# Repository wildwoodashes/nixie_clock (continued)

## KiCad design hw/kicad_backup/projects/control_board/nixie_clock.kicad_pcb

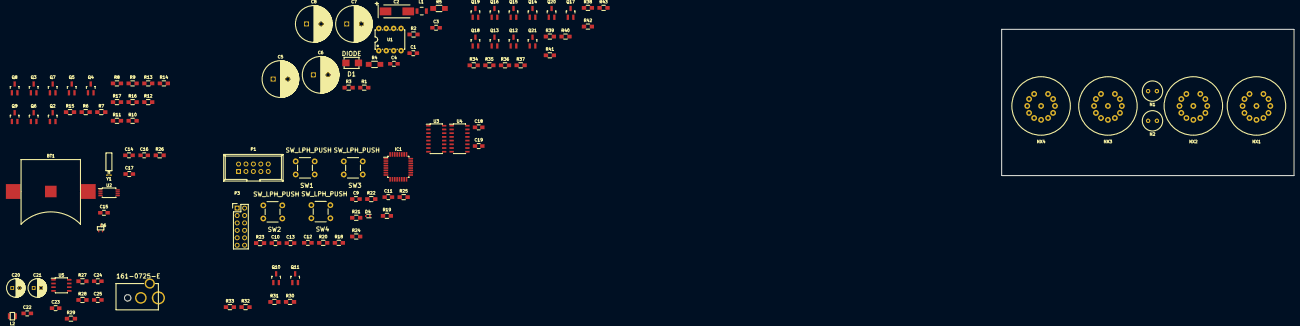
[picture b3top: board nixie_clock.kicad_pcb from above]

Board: 2 copper layers, 100.0 x 50.0 mm, 115 parts (1 on the bottom side), 109 nets, no tracks yet.

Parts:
BT1: BATTERY; 3026_bat_clip
C1, C3, C9, C10, C11, C12, C13, C17, C24, C25: 0.1uF; C_0805_HandSoldering
C2: 68uF; TantalC_SizeD_EIA-7343_HandSoldering
C4, C16: 100pF; C_0805_HandSoldering
C5, C6, C7, C8: 47uF; C_Radial_D12.5_L25_P5
C14, C15: 11pF; C_0805_HandSoldering
C18, C19: 0.1u; C_0805_HandSoldering
C20, C21: 22uF; C_Radial_D6.3_L11.2_P2.5
C22, C23: 10uF; C_0805_HandSoldering
CON1: 161-0725-E
D1: DIODE; DO-214AA-2
D4: D; SOD-523
D6: DIODE; SC-70
IC1: ATMEGA168A-A; TQFP-32_7x7mm_Pitch0.8mm
L1: 150u; Neosid_Inductor_SM-NE30_SMD1210
L2: 2.2uH; ind_2518
N1, N2: C2A; neon_ind
NX1, NX2, NX3, NX4: IN-8; pl27-1pd
P1: CONN_02X05; IDC_Header_Straight_10pins
P3: CONN_02X06; Pin_Header_Straight_2x06
Q1: IPB50R199CP; to263
Q2, Q3, Q6, Q7, Q10, Q11, Q12, Q13, Q14, Q15, Q16, Q17, Q18, Q19, Q20, Q21: MPSA42; SOT-23_Handsoldering
Q4, Q5, Q8, Q9: MPSA92; SOT-23_Handsoldering
R1, R2, R22, R23, R24, R25, R27, R28: 10k; R_0805_HandSoldering
R3: .050; R_0805_HandSoldering
R4: 1.123MEG; R_1206_HandSoldering
R5: 18k; R_1206_HandSoldering
R6, R7, R12, R13, R20, R21, R32, R33, R34, R35, R36, R37, R38, R39, R40, R41, R42, R43: 4.7k; R_0805_HandSoldering
R8, R9, R14, R15: 100k; R_0805_HandSoldering
R10, R11, R16, R17: 12k; R_0805_HandSoldering
R18, R19: 100; R_0805_HandSoldering
R26: 1k; R_0805_HandSoldering
R29: 33.2k; R_0805_HandSoldering
R30, R31: 24k; R_0805_HandSoldering
SW1, SW2, SW3, SW4: SW_LPH_PUSH; LPH
U1: MAX1771; PDIP-8
U2: MCP7940N; TSSOP-8_4.4x3mm_Pitch0.65mm
U3, U4: 74HC595; SOIC-16_3.9x9.9mm_Pitch1.27mm
U5: TPS563208; SOIC-8_3.9x4.9mm_Pitch1.27mm
Y1: 32.768kHz; VT200F-6PF20PPM

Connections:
+3V3: C18.1, C19.1, U3.16, U4.16
+12V: C2.1, C3.1, C22.1, C23.1, C24.1, CON1.1, L1.1, R28.2, U1.2, U5.3
/Colon Tubes/SEL_DOT_BOT: R33.2, U4.3
/Colon Tubes/SEL_DOT_TOP: R32.2, U4.2
/MCU/CYA0: IC1.7, P3.3
/MCU/CYA1: IC1.8, P3.5
/MCU/CYA2: IC1.23, P3.7
/MCU/CYA3: IC1.24, P3.9
/MCU/CYA4: IC1.25, P3.11
/MCU/CYA5: IC1.30, P3.10
/MCU/CYA6: IC1.31, P3.8
/MCU/CYA7: IC1.19, P3.4
/MCU/CYA8: IC1.22, P3.6
/MCU/MCU RTC/RTC_MFP: IC1.32, R25.2, U2.7
/MCU/MCU RTC/RTC_SCL: IC1.28, R24.2, U2.6
/MCU/MCU RTC/RTC_SDA: IC1.27, R23.2, U2.5
/MCU/MCU Shift Registers/OE: IC1.13, U3.13, U4.13
/MCU/MCU Shift Registers/RCLK: IC1.14, U3.12, U4.12
/MCU/MCU Shift Registers/SCLR: IC1.12, U3.10, U4.10
/MCU/MCU Shift Registers/SER: R20.2, U3.14
/MCU/MCU Shift Registers/SRCLK: R21.2, U3.11, U4.11
/Nixie Control/MCU_SEL_EIGHT: R41.1, U4.15
/Nixie Control/MCU_SEL_FIVE: R35.1, U3.5
/Nixie Control/MCU_SEL_FOUR: R42.1, U3.4
/Nixie Control/MCU_SEL_NINE: R43.1, U4.1
/Nixie Control/MCU_SEL_ONE: R6.1, R7.1, R12.1, R13.1, R34.1, R36.1, R38.1, R40.1, U3.1, U3.2, U3.3, U3.15, U4.4, U4.5, U4.6, U4.7
/Nixie Control/MCU_SEL_SEVEN: R39.1, U3.7
/Nixie Control/MCU_SEL_SIX: R37.1, U3.6
/Nixie Power Supply/180V_SHDN: IC1.26, R1.2, U1.4
/Nixie Tubes/NIXIE_EIGHT_CAT: NX1.8, NX2.8, NX3.8, NX4.8, Q19.3
/Nixie Tubes/NIXIE_FIVE_CAT: NX1.5, NX2.5, NX3.5, NX4.5, Q13.3
/Nixie Tubes/NIXIE_FOUR_CAT: NX1.4, NX2.4, NX3.4, NX4.4, Q20.3
/Nixie Tubes/NIXIE_NINE_CAT: NX1.9, NX2.9, NX3.9, NX4.9, Q21.3
/Nixie Tubes/NIXIE_ONE_CAT: NX1.1, NX2.1, NX3.1, NX4.1, Q14.3
/Nixie Tubes/NIXIE_SEVEN_CAT: NX1.7, NX2.7, NX3.7, NX4.7, Q17.3
/Nixie Tubes/NIXIE_SIX_CAT: NX1.6, NX2.6, NX3.6, NX4.6, Q15.3
/Nixie Tubes/NIXIE_THREE_CAT: NX1.3, NX2.3, NX3.3, NX4.3, Q18.3
/Nixie Tubes/NIXIE_TWO_CAT: NX1.2, NX2.2, NX3.2, NX4.2, Q16.3
/Nixie Tubes/NIXIE_ZERO_CAT: NX1.10, NX2.10, NX3.10, NX4.10, Q12.3
GND: BT1.2, C1.2, C2.2, C3.2, C5.2, C6.2, C7.2, C8.2, C9.2, C10.2, C11.2, C12.2, C13.2, C14.1, C15.1, C16.1, C17.1, C18.2, C19.2, C20.2, C21.2, C22.2, C23.2, C24.2, CON1.3, IC1.3, IC1.5, IC1.21, P1.4, P1.6, P1.8, P1.10, P3.12, Q2.1, Q3.1, Q6.1, Q7.1, Q10.1, Q11.1, Q12.1, Q13.1, Q14.1, Q15.1, Q16.1, Q17.1, Q18.1, Q19.1, Q20.1, Q21.1, R2.2, R3.2, R27.1, SW1.1, SW1.2, SW2.1, SW2.2, SW3.1, SW3.2, U1.6, U1.7, U2.4, U3.8, U4.8, U5.1
unnamed: BT1.1, D6.1
unnamed: C1.1, U1.5
unnamed: C4.1, R2.1, R4.1, U1.3
unnamed: C4.2, C5.1, C6.1, C7.1, C8.1, D1.2, R4.2, R5.1
unnamed: C9.1, C10.1, C11.1, IC1.4, IC1.6, IC1.18
unnamed: C12.1, IC1.20
unnamed: C13.1, IC1.29, P1.5, R22.1, SW1.3, SW1.4
unnamed: C14.2, U2.1, Y1.1
unnamed: C15.2, U2.2, Y1.2
unnamed: C16.2, R26.1, U2.3
unnamed: C17.2, U2.8
unnamed: C20.1, C21.1, L2.1
unnamed: C25.1, U5.6
unnamed: C25.2, L2.2, U5.2
unnamed: D1.1, L1.2, Q1.2
unnamed: D4.1, P1.2
unnamed: D6.2, R26.2
unnamed: IC1.1, SW4.3, SW4.4
unnamed: IC1.2, SW3.3, SW3.4
unnamed: IC1.9, SW2.3, SW2.4
unnamed: IC1.10, R18.1
unnamed: IC1.11, R19.1
unnamed: IC1.15, P1.1, R20.1
unnamed: IC1.16, P1.9
unnamed: IC1.17, P1.7, R21.1
unnamed: N1.1, R30.1
unnamed: N1.2, Q11.3
unnamed: N2.1, R31.1
unnamed: N2.2, Q10.3
unnamed: NX1.11, R10.2
unnamed: NX2.11, R11.2
unnamed: NX3.11, R17.2
unnamed: NX4.11, R16.2
unnamed: Q1.1, U1.1
unnamed: Q1.3, R3.1, U1.8
unnamed: Q2.2, R6.2
unnamed: Q2.3, Q4.2, R8.1
unnamed: Q3.2, R7.2
unnamed: Q3.3, Q5.2, R9.1
unnamed: Q4.1, R8.2
unnamed: Q4.3, R10.1
unnamed: Q5.1, R9.2
unnamed: Q5.3, R11.1
unnamed: Q6.2, R12.2
unnamed: Q6.3, Q8.2, R14.1
unnamed: Q7.2, R13.2
unnamed: Q7.3, Q9.2, R15.1
unnamed: Q8.1, R14.2
unnamed: Q8.3, R16.1
unnamed: Q9.1, R15.2
unnamed: Q9.3, R17.1
unnamed: Q10.2, R32.1
unnamed: Q11.2, R33.1
unnamed: Q12.2, R34.2
unnamed: Q13.2, R35.2
unnamed: Q14.2, R36.2
unnamed: Q15.2, R37.2
unnamed: Q16.2, R38.2
unnamed: Q17.2, R39.2
unnamed: Q18.2, R40.2
unnamed: Q19.2, R41.2
unnamed: Q20.2, R42.2
unnamed: Q21.2, R43.2
unnamed: R23.1, R24.1, R25.1
unnamed: R27.2, R29.2, U5.4
unnamed: R28.1, U5.5
unnamed: R30.2, R31.2
unnamed: SW4.1, SW4.2
unnamed: U3.9, U4.14

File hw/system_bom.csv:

Id,Designator,Package,Quantity,Designation,Supplier and ref,Vendor Part Number,Vendor Quantity
Control Board,,,,,,,
1,D4,SOD-523-2,1,D,Mouser,865-XBS053V15R-G,1
2,F1,MRF2,1,FUSE,Mouser,530-MRF2,1
3,L1,SRU1048-151Y,1,150u,Mouser,652-SRU1048-151Y,1
4,Q1,to263,1,IPB50R199CP,Mouser,512-FDB33N25TM,1
5,"R18,R8,R9",R_0805_HandSoldering,3,330,Mouser,588-AS08J1003ET,4
6,U2,SOIC-8_3.9x4.9mm_Pitch1.27mm,1,MCP7940N,Mouser,579-MCP7940N-I/SN,1
7,D6,SOT-323,1,D_Schottky_x2_ACom_KKA,Mouser,863-MMBD717LT1G,1
8,"C1,C3,C9,C10,C11,C12,C13,C17,C24,C25",C_0805_HandSoldering,10,0.1uF,Mouser,710-885012207072,10
9,C2,TantalC_SizeD_EIA-7343_HandSoldering,1,68uF,Mouser,80-T495D686K20ATE150,1
10,"C4,C16",C_0805_HandSoldering,2,100pF,Mouser,81-GRM21A5C2E101JW1D,2
11,"C5,C6,C7,C8",C_Radial_D12.5_L25_P5,4,47uF,Mouser,647-UVR2E470MHD,4
12,"C18,C19",C_0805_HandSoldering,2,0.1u,Mouser,710-885012207072,2
13,"C20,C21",C_Radial_D6.3_L11.2_P2.5,2,22uF,Mouser,647-RNS1D220MDS1JT,2
14,"C22,C23",C_0805_HandSoldering,2,10uF,Mouser,81-GRM21BR61E106KA3L,2
15,D1,DO-214AA-2,1,D,Mouser,821-ES2F,1
16,IC1,TQFP-32_7x7mm_Pitch0.8mm,1,ATMEGA168A-A,Mouser,556-ATMEGA48A-AU,1
17,L2,ind_2518,1,LBR2518T2R2M,Mouser,963-LBR2518T2R2M,1
18,P2,Pin_Header_Straight_2x06,1,CONN_02X06,Mouser,NA,0
19,"R1,R2,R10,R13,R15,R16",R_0805_HandSoldering,6,10k,Mouser,71-CRCW0805-10K-E3,6
20,R3,R_0805_HandSoldering,1,0.1,Mouser,652-CRL0805FWR100ELF,1
21,R4,R_1206_HandSoldering,1,1.123MEG,Mouser,660-RK73H2BTTD1134F,1
22,"R6,R7",R_0805_HandSoldering,2,100,Mouser,588-AS08J1000ET,2
23,"R11,R12",R_0805_HandSoldering,2,2k,Mouser,660-RK73H2ATTD2001F,2
24,R14,R_0805_HandSoldering,1,1k,Mouser,588-AS08J1001ET,1
25,R17,R_0805_HandSoldering,1,33.2k,Mouser,660-RK73H2ATTD3322F,1
26,U1,PDIP-8,1,MAX1771,Mouser,700-MAX1771CSA,1
27,"U3,U4",SOIC-16_3.9x9.9mm_Pitch1.27mm,2,74HC595,Mouser,511-M74HC595YRM13TR,2
28,U5,SOIC-8_3.9x4.9mm_Pitch1.27mm,1,TPS563208,Mouser,595-TPS5410DR,1
29,P1,Pin_Header_Straight_2x12,1,CONN_02X12,Mouser,710-61202421621,1
30,"P4,P5,P6,P7",MountingHole_3.2mm_M3_ISO7380_Pad,4,CONN_01X01,Mouser,NA,0
31,"SW1,SW2,SW3,SW4",FSMRA5JH,4,SW_LPH_PUSH,Mouser,2-1825027-0,3
,,,,,Mouser,FSMRA3JH,1
32,"D2,D3,D5",LED_0603,3,LTST-C190GKT,Mouser,859-LTST-C190GKT,3
33,R5,R_0805_HandSoldering,1,18k,Mouser,652-CR1206FX-1802ELF,1
34,"C14,C15",C_0603_HandSoldering,2,11pF,Mouser,81-GRM185C1H110FA01D,2
35,Y1,ABS25,1,32.768kHz,Mouser,815-ABS25-32.768K6-T,1
36,P3,IDC_Header_Straight_10pins,1,CONN_02X05,Mouser,NA,0
37,BT1,smtu2032-c,1,BATTERY,Mouser,614-SMTU2032-C.TR,1
38,CON1,161-0725-E,1,161-0725-E,Mouser,161-0725-E,1
,NA,NA,,Wall Wart,Ebay,391444968888,1
,,,,,,,
,,,,,,,
,,,,,,,
Tube Shield,,,,,,,
1,"NX2,NX1,NX4,NX3",pl27-1pd,4,IN-8,eBay,NA,4
2,"P5,P4,P3",MountingHole_3.2mm_M3_ISO14580_Pad,3,CONN_01X01,NA,NA,0
3,P2,MountingHole_3.2mm_M3_ISO7380_Pad,1,CONN_01X01,NA,NA,0
4,"R43,R42,R41,R40,R39,R38,R37,R36,R35,R34,R33,R32,R13,R12,R7,R6",R_0805_HandSoldering,16,4.7k,Mouser,ERJ-6GEYJ472V,16
5,"R31,R30",R_0805_HandSoldering,2,24k,Mouser,ERJ-6GEYJ243V,2
6,"R17,R16,R11,R10",R_0805_HandSoldering,4,12k,Mouser,ERJ-6GEYJ123V,4
7,"R15,R14,R9,R8",R_0805_HandSoldering,4,100k,Mouser,AS08J1003ET,4
8,"Q21,Q20,Q19,Q18,Q17,Q16,Q15,Q14,Q13,Q11,Q10,Q7,Q6,Q3,Q2,Q12",SOT-23_Handsoldering,16,MPSA42,Mouser,MMBTA42LT1G,16
9,"Q9,Q8,Q5,Q4",SOT-23_Handsoldering,4,MPSA92,Mouser,MMBTA92LT1G,4
10,P1,Pin_Header_Straight_2x12,1,CONN_02X12,Mouser,710-61202421621,1
11,"N2,N1",neon_ind,2,C2A,eBay,NA,2
,,,,,,,
,,,,,,,
,,,130,,,,

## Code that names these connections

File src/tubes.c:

//tubes.c
//A. Briggs
//10/09/16
#define F_CPU 8000000 //8Mhz clock

#include <util/delay.h>
#include "tubes.h"

#define TRUE 1
#define FALSE 0

#define SER PB3
#define SRCLK PB5
#define SCLR_N PB0
#define OE_N PB1
#define RCLK PB2
#define EN_180V PC3
#define COL_SEL PB7

// Initialize SPI Master Device (without interrupt)
void spi_init_master (void)
{
    // Set MOSI, SCK, SCLR_N, OE_N, and RCLK as Output
    DDRB |= (1<<SER)|(1<<SRCLK)|(1<<SCLR_N)|(1<<OE_N)|(1<<RCLK);

    // Enable COL_SEL pin
    DDRB |= (1<<COL_SEL);

    // Enable SHTDN function
    DDRC |= (1<<EN_180V);
    PORTC |= (1<<EN_180V);
 
    // Enable SPI, Set as Master
    //Prescaler: Fosc/16, disable Interrupts
    SPCR = (1<<SPE)|(1<<MSTR)|(1<<SPR0);

    PORTB |= (1<<SCLR_N); // Disable CLR
    PORTB |= (1<<OE_N);   // Disable output initially

    // Disable power supply by default
    PORTC &= ~(1<<EN_180V);
}

void nixie_tube_supply (uint8_t status){
    // Set power supply based on intput
    if(status == TRUE){
        PORTC |= (1<<EN_180V);
    }
    else{
        PORTC &= ~(1<<EN_180V);
    }
}

/********************set_nixie*************************/
// Set the different annondes/cathodes
//
//Function to send and receive data for both master and slave
void set_tubes (uint8_t nix0, uint8_t nix1, uint8_t nix2, uint8_t nix3, uint8_t colon_en)
{
    uint8_t upper = 0;
    uint8_t lower = 0;

    uint8_t n0_digit = dec_to_bin_normal(nix0);
    uint8_t n1_digit = dec_to_bin_normal(nix1);
    uint8_t n2_digit = dec_to_bin_normal(nix2);
    uint8_t n3_digit = dec_to_bin_fucked(nix3);

    PORTB &= ~(1<<RCLK); // make sure parallel clock is low
    PORTB |= (1<<OE_N);  // Disable output initially

    upper =  (n1_digit<<4) | n0_digit;
    lower =  (n3_digit<<4) | n2_digit;

    write_shift_reg(upper);
    write_shift_reg(lower);

    PORTB |= (1<<RCLK); // create rising edge on parallel clock
    _delay_us(10);
    PORTB &= ~(1<<RCLK); // toggle parallel clock low

    PORTB &= ~(1<<OE_N); // enable output

    // Set Colon based on input
    if(colon_en == TRUE){
        PORTB |= (1<<COL_SEL);
    }
    else{
        PORTB &= ~(1<<COL_SEL);
    }
}
/**************************************************************/

/********************dec_to_bin_ordered*************************/
// Convert decimal number to binary for SN74141
//
// Conversion table:
//    DCBA
// 4'b0000 = 0
// 4'b0001 = 1
// 4'b0010 = 2
// 4'b0011 = 3
// 4'b0100 = 4
// 4'b0101 = 5
// 4'b0110 = 6
// 4'b0111 = 7
// 4'b1000 = 8
// 4'b1001 = 9
// 4'b1010-4'b1111 = RESERVED! DO NOT USE!
// This function is overkill, but helps keep only legal values assinged
uint8_t dec_to_bin_normal (uint8_t decimal){
    uint8_t ret_bin = 0;

    switch(decimal){
        case 0 : 
            ret_bin = 0b0000;
            break;
        case 1 : 
            ret_bin = 0b0001;
            break;
        case 2 : 
            ret_bin = 0b0010;
            break;
        case 3 : 
            ret_bin = 0b0011;
            break;
        case 4 : 
            ret_bin = 0b0100;
            break;
        case 5 : 
            ret_bin = 0b0101;
            break;
        case 6 : 
            ret_bin = 0b0110;
            break;
        case 7 : 
            ret_bin = 0b0111;
            break;
        case 8 : 
            ret_bin = 0b1000;
            break;
        case 9 : 
            ret_bin = 0b1001;
            break;
        default:
            ret_bin = 0b0000;
    }

    return ret_bin;
}

/********************dec_to_bin_fucked*************************/
// Convert decimal number to binary for SN74141
//
// Conversion table:
//    DCBA
// 4'b0000 = 0
// 4'b0001 = 1
// 4'b0010 = 2
// 4'b0011 = 3
// 4'b0100 = 4
// 4'b0101 = 5
// 4'b0110 = 6
// 4'b0111 = 7
// 4'b1000 = 8
// 4'b1001 = 9
// 4'b1010-4'b1111 = RESERVED! DO NOT USE!
// Nixie tube 4 has a pin swap (DOH!) -- unfuck that here
uint8_t dec_to_bin_fucked (uint8_t decimal){
    uint8_t ret_bin = 0;

    switch(decimal){
        case 0 : 
            ret_bin = 0b0000;
            break;
        case 1 : 
            ret_bin = 0b0001;
            break;
        case 2 : 
            ret_bin = 0b0010;
            break;
        case 3 : 
            ret_bin = 0b0011;
            break;
        case 4 : 
            ret_bin = 0b0101;
            break;
        case 5 : 
            ret_bin = 0b0100;
            break;
        case 6 : 
            ret_bin = 0b0110;
            break;
        case 7 : 
            ret_bin = 0b0111;
            break;
        case 8 : 
            ret_bin = 0b1000;
            break;
        case 9 : 
            ret_bin = 0b1001;
            break;
        default:
            ret_bin = 0b0000;
    }

    return ret_bin;
}

/********************write_shift_reg*************************/
// Write a value to the RTC
//
//Function to send and receive data for both master and slave
void write_shift_reg (uint8_t data)
{
    // Load data into the buffer
    SPDR = data;
 
    //Wait until transmission complete
    while(!(SPSR & (1<<SPIF) ));
}
/**************************************************************/

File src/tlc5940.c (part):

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//8.6.10
#include "tlc5940.h"

#define DIG1 (1<<PD1)
#define DIG2 (1<<PD3)
#define DIG3 (1<<PD2)
#define DIG4 (1<<PD0)

uint8_t ASCI_2_7SEG[11] = 
 {0b10111011,				//0
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void tlc5940_init(void){
  uint8_t i = 0;

  //PB2 = BLANK, PB0 = XLAT, PD7 = VPRG
  DDRB |= (1<<BLANK)|(1<<XLAT);
  DDRD |= (1<<VPRG);
  
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
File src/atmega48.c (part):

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//
uint8_t chk_button_momt(uint8_t button) {
  static uint16_t state[3] = {0,0,0}; //holds present state for 3 seperate buttons
  uint8_t switch_bit = PD3;
  
  switch(button){
		case(0):
			switch_bit = PD3;
			break;
		case(1):
			switch_bit = PD4;
			break;
		case(2):
			switch_bit = PD5;
			break;
  }
  
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//
uint8_t chk_button_hold(uint8_t button) {
  static uint16_t state[3] = {0,0,0}; //holds present state for 3 seperate buttons
  uint8_t switch_bit = PD3;
  
  switch(button){
		case(0):
			switch_bit = PD3;
			break;
		case(1):
			switch_bit = PD4;
			break;
		case(2):
			switch_bit = PD5;
			break;
  }
  
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    uint8_t user_override = FALSE;

    // Power off nixie supply ASAP
	PORTC &= ~(1<<PC3); //keep Nixie Supply off at poweron
    DDRC |= (1<<PC3);   // Set PC3 as an output
	
	//Buttons
	DDRD |= (1<<PD6) | (1<<PD7); // Set PD6 and PD7 as outputs
	DDRD &= ~(1<<PD3); // SW4
	DDRD &= ~(1<<PD4); // SW3
	DDRD &= ~(1<<PD5); // SW2
	PORTD |= (1<<PD3) | (1<<PD4) | (1<<PD5); //enable pullups
	PORTD |= (1<<PD6); 		//keep LEDs off to start
	PORTD |= (1<<PD7); 		//keep LEDs off to start


	// PORTD &= ~(1<<PD6);
	// PORTD &= ~(1<<PD7);

	twi_init();
	spi_init_master();
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			
			// Send out next bit on LED
			if(read_data>>i & 0x01){
				PORTD &= ~(1<<PD6);	
			}
			else{
				PORTD |= (1<<PD6);	
			}
			
            set_tubes(2, i, FALSE);
			// Turn on second LED on last bit
			if(i==7){
				PORTD &= ~(1<<PD7);	
                set_tubes(2, i, TRUE);
			}
			// Turn off Second LED on first bit
			else if(i==0){
				PORTD |= (1<<PD7);	
			}

			
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
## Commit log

2016-09-27 Add ignore for executables
    Add ignore for executables for the time being. I will decide later if I
    want these in the repo.
2016-09-29 Update documentation
    Update PDF of schematic and BOM.
2016-10-12 Initial code commit
    This is the initial code commit. It is adapted from the previous "power
    supply" project.
2016-10-17 Switch tube_board to driver chips
    Convert from Mux'd control to direct drive with 74141 based chips.
    Increase size of board. Should probably reduce this as it looks like the
    board is too large.
2016-11-06 Update
    Begin work on updating for rev1.1.
2016-11-07 Schematic Work Complete
    Check in schematic work before touching PCB. This should give me a point
    to go back to if it all goes to hell.
2016-11-11 Updates to BOM
    Start to update BOM for 180V supply
2016-11-20 Complete with errors
    Check in before moving header. Currently the headers don't match up. If
    I'm going to connect them with standard header I need to move it
    significantly. Check in as a roll back point.
2016-12-23 Final Release
    Update with trimming and bug fixes. This is what is being delivered as a
    V1.1.0 release.
2016-12-23 Add Tools
    Add tools to help debug elsewhere if needed.
2016-12-24 Fix issue with interrupt lock up
    Resolved issue caused by interrupt locking up the I2C.
